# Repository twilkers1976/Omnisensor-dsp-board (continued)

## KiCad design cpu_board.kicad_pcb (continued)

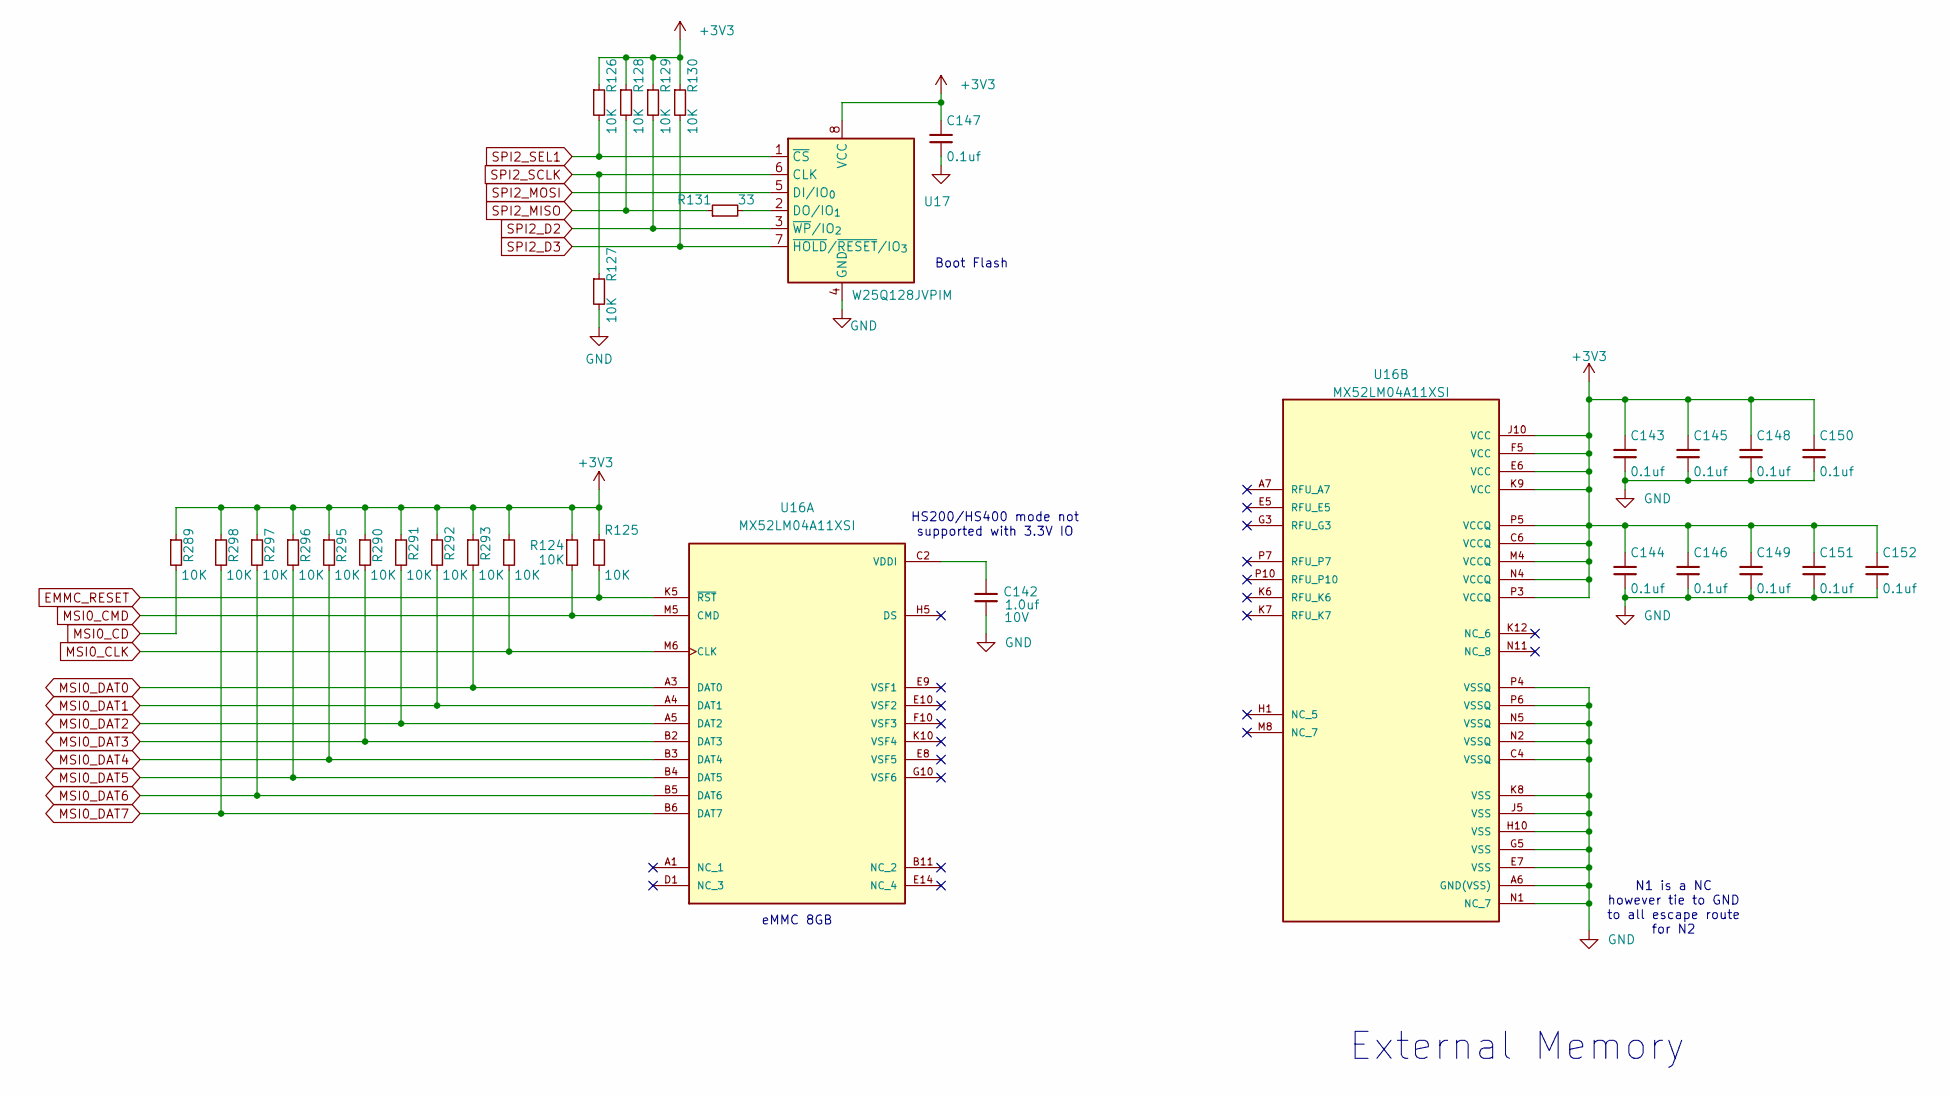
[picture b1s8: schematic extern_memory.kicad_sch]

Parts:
C142: 1.0uf; C_0402_1005Metric; Voltage 10V; Rating 16V; Part Number EMK105BJ105KV-F
C143, C144, C145, C146, C147, C148, C149, C150, C151, C152: 0.1uf; C_0402_1005Metric; Rating 50V; Part Number 04025C104KAT2A
R124, R125, R126, R127, R128, R129, R130, R289, R290, R291, R292, R293, R294, R295, R296, R297, R298: 10K; R_0402_1005Metric; Part Number RMCF0402FT10K0
R131: 33; R_0402_1005Metric; Part Number RMCF0402FT33R0
U16: MX52LM04A11XSI; BGA153N50P14X14_1300X1150X100N; PARTREV N/A
U17: W25Q128JVPIM; WSON-8-1EP_6x5mm_P1.27mm_EP3.4x4mm; Part Number W25Q128JVPIM

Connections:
+3V3: C143.1, C144.1, C145.1, C146.1, C147.1, C148.1, C149.1, C150.1, C151.1, C152.1, R124.1, R125.1, R126.1, R128.1, R129.1, R130.1, R289.1, R290.1, R291.1, R292.1, R293.1, R294.1, R295.1, R296.1, R297.1, R298.1, U16.C6 (VCCQ), U16.E6 (VCC), U16.F5 (VCC), U16.J10 (VCC), U16.K9 (VCC), U16.M4 (VCCQ), U16.N4 (VCCQ), U16.P3 (VCCQ), U16.P5 (VCCQ), U17.8 (VCC); also elsewhere on the board
EMMC_RESET: R125.2, U16.K5 (~RST); also elsewhere on the board
GND: C142.2, C143.2, C144.2, C145.2, C146.2, C147.2, C148.2, C149.2, C150.2, C151.2, C152.2, R127.2, U16.A6 (GND(VSS)), U16.C4 (VSSQ), U16.E7 (VSS), U16.G5 (VSS), U16.H10 (VSS), U16.J5 (VSS), U16.K8 (VSS), U16.N1 (NC_7), U16.N2 (VSSQ), U16.N5 (VSSQ), U16.P4 (VSSQ), U16.P6 (VSSQ), U17.4 (GND); also elsewhere on the board
MSI0_CD: R289.2; also elsewhere on the board
MSI0_CLK: R294.2, U16.M6 (CLK); also elsewhere on the board
MSI0_CMD: R124.2, U16.M5 (CMD); also elsewhere on the board
MSI0_DAT0: R293.2, U16.A3 (DAT0); also elsewhere on the board
MSI0_DAT1: R292.2, U16.A4 (DAT1); also elsewhere on the board
MSI0_DAT2: R291.2, U16.A5 (DAT2); also elsewhere on the board
MSI0_DAT3: R290.2, U16.B2 (DAT3); also elsewhere on the board
MSI0_DAT4: R295.2, U16.B3 (DAT4); also elsewhere on the board
MSI0_DAT5: R296.2, U16.B4 (DAT5); also elsewhere on the board
MSI0_DAT6: R297.2, U16.B5 (DAT6); also elsewhere on the board
MSI0_DAT7: R298.2, U16.B6 (DAT7); also elsewhere on the board
unnamed: C142.1, U16.C2 (VDDI)
unnamed: R131.2, U17.2 (DO/IO_{1})
SPI2_D2: R129.2, U17.3 (~WP/IO_{2}); also elsewhere on the board
SPI2_D3: R130.2, U17.7 (~HOLD/~RESET/IO_{3}); also elsewhere on the board
SPI2_MISO: R128.2, R131.1; also elsewhere on the board
SPI2_MOSI: U17.5 (DI/IO_{0}); also elsewhere on the board
SPI2_SCLK: R127.1, U17.6 (CLK); also elsewhere on the board
SPI2_SEL1: R126.2, U17.1 (~CS); also elsewhere on the board

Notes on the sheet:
External Memory
eMMC 8GB
HS200/HS400 mode not supported with 3.3V IO
Boot Flash
N1 is a NC however tie to GND to all escape route for N2

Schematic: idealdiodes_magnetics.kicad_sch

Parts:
C53, C140: 1000pf; C_1808_4520Metric; Voltage 3KV; Rating 3KV; Part Number CHV1808N3K0102MXT
C54: 0.047uf; C_0603_1608Metric; Voltage 16V; Rating 16V; Part Number CL10B473KO8NNNC
D1: DDZ9709S-7; Rating 24V; PARTREV 13 - 2
D2: PTVS58VS1UR,115; TVS_PTVS58VS1UR; PARTREV Rev. 3
J1: JXK0-0190NL; JK0-0177NL_PUL; Part Number JXK0-0190NL
Q1, Q2, Q3, Q4, Q5, Q6, Q7, Q8: PSMN075-100MSE; TRANS_PSMN075-100MSE; PARTREV 24 July 2024
R1, R2, R3, R4: 75; R_0603_1608Metric; Part Number RN73H1JTTD75R0F100
R5: 0; R_0402_1005Metric; Part Number RMCF0402ZT0R00
U1: LT4321IUF_PBF; PARTREV 0

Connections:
+3V3: J1.13 (CA_1), J1.16 (CA_1); also elsewhere on the board
/PoE/IdealDiodes_Magnetics/BG12: Q2.4, U1.14 (BG12)
/PoE/IdealDiodes_Magnetics/BG36: Q4.4, U1.13 (BG36)
/PoE/IdealDiodes_Magnetics/BG45: Q6.4, U1.8 (BG45)
/PoE/IdealDiodes_Magnetics/BG78: Q8.4, U1.7 (BG78)
/PoE/IdealDiodes_Magnetics/DATA1_1: J1.17 (VDC1+), Q1.1, Q1.2, Q1.3, Q2.MB, U1.15 (IN12)
/PoE/IdealDiodes_Magnetics/DATA1_2: J1.18 (VDC1=), Q3.1, Q3.2, Q3.3, Q4.MB, U1.2 (IN36)
/PoE/IdealDiodes_Magnetics/DATA2_1: J1.19 (VDC2+), Q5.1, Q5.2, Q5.3, Q6.MB, U1.3 (IN45)
/PoE/IdealDiodes_Magnetics/DATA2_2: J1.20 (VDC2-), Q7.1, Q7.2, Q7.3, Q8.MB, U1.6 (IN78)
/PoE/IdealDiodes_Magnetics/TG12: Q1.4, U1.16 (TG12)
/PoE/IdealDiodes_Magnetics/TG36: Q3.4, U1.1 (TG36)
/PoE/IdealDiodes_Magnetics/TG45: Q5.4, U1.4 (TG45)
/PoE/IdealDiodes_Magnetics/TG78: Q7.4, U1.5 (TG78)
GND: C53.2; also elsewhere on the board
LED1_CATHODE: J1.15 (CA_2); also elsewhere on the board
LED2_CATHODE: J1.14 (CA_2); also elsewhere on the board
MD1+: J1.11 (MD1+); also elsewhere on the board
MD1-: J1.10 (MD1-); also elsewhere on the board
MD2+: J1.4 (MD2+); also elsewhere on the board
MD2-: J1.5 (MD2-); also elsewhere on the board
MD3+: J1.3 (MD3+); also elsewhere on the board
MD3-: J1.2 (MD3-); also elsewhere on the board
MD4+: J1.8 (MD4+); also elsewhere on the board
MD4-: J1.9 (MD4-); also elsewhere on the board
unnamed: C53.1, R1.2, R2.2, R3.2, R4.2
unnamed: C140.1, J1.23, J1.24
unnamed: J1.12 (MDCT1), R4.1
unnamed: J1.6 (MDCT2), R3.1
unnamed: J1.1 (MDCT3), R2.1
unnamed: J1.7 (MDCT4), R1.1
unnamed: D1.A, U1.11 (EN)
unnamed: R5.1, U1.10 (~EN)
PGND: C140.2; also elsewhere on the board
VPORTN: C54.2, D2.A, Q2.1, Q2.2, Q2.3, Q4.1, Q4.2, Q4.3, Q6.1, Q6.2, Q6.3, Q8.1, Q8.2, Q8.3, U1.9 (OUTN), U1.17 (OUTN); also elsewhere on the board
VPORTP: C54.1, D1.K, D2.C, Q1.MB, Q3.MB, Q5.MB, Q7.MB, R5.2, U1.12 (OUTP); also elsewhere on the board

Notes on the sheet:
Ideal Diodes and Magnetics
do we need ESD on these, SP05045HTG
IN FROM PoE+ PSE

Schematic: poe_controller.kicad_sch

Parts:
C93: 100pf; C_0603_1608Metric; Rating 250V; Part Number CHV0603N250101FCT
C94: 0.047uf; C_0805_2012Metric; Rating 16V; Part Number C0805C473F4GACTU
C95: 0.01uf; C_0603_1608Metric; Rating 16V; Part Number KGM15AR71C103KT
C96: 10uf; PNSC-FT-V-83x83-2_V; Rating 100V; Part Number PCV2A100MCL1GS
C97: 2.2uf; C_1210_3225Metric; Rating 100V; Part Number GRM32ER72A225KA35L
C98, C107: 10uf; C_1206_3216Metric; Rating 16V; Part Number C1206C106M4RACAUTO
C99: 0.1uf; C_0603_1608Metric; Rating 50V; Part Number KGM15BR71H104KT
C100: DNP-OPT; C_0402_1005Metric; not fitted
C101: 3.3nf; C_0603_1608Metric; Rating 16V; Part Number C0603C332J4GACTU
C102: 47pf; C_1206_3216Metric; Rating 1KV; Part Number CHV1206N1K0470FCT
C103: 220pf; C_0603_1608Metric; Rating 250V; Part Number CHV0603N250221GCT
C104: 1uf; C_0603_1608Metric; Rating 50V; Part Number 06035C105KAT2A
C105: DNP-OPT; C_1812_4532Metric; Rating 2KV; not fitted
C106: 4.7nf; C_1812_4532Metric; Rating 25V; Part Number 885012210005
C108: 470pf; C_1206_3216Metric; Rating 600V; Part Number GRM31A7U2J471JW31D
C109: 2.2nf; C_0603_1608Metric; Rating 25V; Part Number GRM188R72A222KA01D
C110, C112: DNP-OPT; C_1206_3216Metric; Rating 16V; Part Number C1206C106M4RACAUTO; not fitted
C111: 22uf; CAP_16SVP22M; Rating 16V; Part Number 16SVP22M
C294: 1uf; C_0805_2012Metric; Rating 16V; Part Number CL21B105KOFVPNE
D4: B2100-13-F; DIOM5336X250N; Part Number B2100-13-F
D5, D7: PTVS58VS1UR,115; TVS_PTVS58VS1UR; Part Number PTVS58VS1UR,115
D6: BAV19WS; D_SOD-323F; Part Number BAV19WS
D8: BAT46WJ_115; SOD323_V; Part Number BAT46WJ,115
D9: DNP-OPT; SOD323_V; Part Number BAT46WJ_115; not fitted
D24: Blue; LED_B1931NG_HVK; Part Number B19Y1NB--20C000113U1930
E1: AUX+; TestPoint_THTPad_D1.0mm_Drill0.5mm; PART REFERENCE E10
E2: AUX-; TestPoint_THTPad_D1.0mm_Drill0.5mm; PART REFERENCE E10
E4: GND_SEC; TestPoint_THTPad_D1.0mm_Drill0.5mm; PART REFERENCE E10
E5: GND; TestPoint_THTPad_D1.0mm_Drill0.5mm; PART REFERENCE E10
L1: 744272332; WE-SL5_BIFILAR; Part Number 744272332
L2: 10uh; IND_DO1608C_COC; Rating 1.5A; Part Number DO1608C-103MLC
L3: 100uh; IND_DO1608C_COC; Rating 500mA; Part Number DO1608C-104MLC
L4: 330nh; DO1813H; Rating 7A; Part Number DO1813H-331MLD
Q9: PSMN075-100MSE; TRANS_PSMN075-100MSE; PARTREV 24 July 2024
Q10: FJV992FMTF; SOT91P240X120-3N; Part Number FJV992FMTF
Q11: XP10TN135N; SOT95P251X112-3N; 5TH VOLTAGE 100; PART REFERENCE Q3
Q12: BSZ520N15NS3G; SON65P330X330X110-9N; Part Number BSZ520N15NS3GATMA1
Q13: MMBT3906; SOT-23; Part Number MMBT3906
Q14: FDMC86160; TRANS_FDMC86102; 5TH VOLTAGE 100V; PART REFERENCE Q2
Q15: MMBT3904; SOT-23; Part Number MMBT3904
R70: 174K; R_0603_1608Metric; Part Number RN73H1JTTD1743F100
R71: 52.3K; R_0603_1608Metric; Part Number CPF0603F52K3C1
R72: 8.2; R_0805_2012Metric; Rating 1/4 Watt; Part Number CRCW08058R20FKEA
R73: 3.3K; R_0603_1608Metric; Rating 1/10 Watt; Part Number MCT06030C3301FP500
R74: 2K; R_0603_1608Metric; Rating 1/10 W; Part Number RN73H1JTTD2001F100
R75: 6.49K; R_0603_1608Metric; Rating 1/10 W; Part Number RN73H1JTTD6491F100
R76: DNP-OPT; R_0603_1608Metric; Rating 1/10 W; Part Number RN73H1JTTD1001F100
R77: 35.7; R_0805_2012Metric; Rating 1/4 W; Part Number CRCW080535R7FKEA
R78: 5.23K; R_0603_1608Metric; Rating 1/10 W; Part Number RN73H1JTTD5231F100
R79: 20; R_0805_2012Metric; Rating 1/4 Watt; Part Number CRCW080520R0FKEA
R80: 107K; R_0603_1608Metric; Rating 1/4 W; Part Number RN73H1JTTD1073F100
R81, R85: 0; R_0402_1005Metric; Part Number RMCF0402ZT0R00
R82: DNP-OPT; R_0603_1608Metric; Rating 1/4 W; not fitted
R83: 10K; R_0402_1005Metric; Part Number RMCF0402FT10K0
R84: 26.1K; R_0603_1608Metric; Part Number RT0603BRD0726K1L
R87: 150; R_1206_3216Metric; Rating 1/4 W; Part Number RK73H2BTTD1500F
R88: 40m; R_0603_1608Metric; Rating 1/10 W; Part Number PE0603FRF070R04L
R89: 100; R_0603_1608Metric; Rating 1/10 W; Part Number RN73H1JTTD1000F100
R90, R91: 27; R_1206_3216Metric; Rating 1/4 W; Part Number CRCW120627R0FKEAC
R92: 47K; R_0603_1608Metric; Rating 1/10 W; Part Number RN73H1JTTD4702F100
R93: 4.7K; R_0603_1608Metric; Rating 1/10 W; Part Number RN73H1JTTD4701F100
R94: 15; R_0603_1608Metric; Rating 1/10 W; Part Number RN73H1JTTD15R0F100
R95: 10K; R_0603_1608Metric; Rating 1/10W; Part Number RN73H1JTTD1002F100
R96: DNP-OPT; R_0805_2012Metric; Rating 1/4 W; not fitted
R97: 3.3K; R_0402_1005Metric; Rating 1/10 W; Part Number RMCF0402FT3K30
R100: DNP-OPT; R_1206_3216Metric; Rating 1/4 W; not fitted
R134, R142: 0; R_1210_3225Metric; Part Number RMCF1210ZT0R00
R303: 0; R_0805_2012Metric; Part Number RMCF0805ZT0R00
T1: 750310742; WE-POE__EP13_PADL1.55W1.27; Part Number 750310742
T2: PE-68386NL; PE-68386NL_PUL; Part Number PE-68386NL
U7: LT4276BIUFDTRPBF; QFN-28_UFD; Part Number LT4276BIUFD#TRPBF
U9: MOC207M; SOIC8_751DZ_ONS_OSI; Part Number MOC207M

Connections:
+3V3: R92.2; also elsewhere on the board
/PoE/PoE_Controller/PVCC: C98.1, L3.1, U7.6 (VCC), U7.7 (VCC), U7.8 (VCC), U7.9 (VCC), U7.21 (VCC)
GND: D24.1, E5.1 (A_1), R134.2, R142.2; also elsewhere on the board
GND_POWER: C93.2, C94.2, C95.2, C96.2, C97.2, C98.2, C99.2, C100.2, C103.2, C106.1, D5.A, D6.2 (A), D7.A, E2.1 (A_1), L1.3, R71.1, R74.1, R76.1, R77.1, R78.1, R80.1, R82.1, R84.1, R88.1, T1.2, T2.2, U7.1 (GND), U7.16 (ISEN-), U7.19 (GND), U7.29 (GND_EP), U9.2
GND_SEC: C106.2, C107.2, C110.2, C111.2, C112.2, C294.2, D8.2, E4.1 (A_1), Q13.3 (C), Q14.1 (S1), Q14.2 (S2), Q14.3 (S3), R90.1, R91.1, R93.2, R95.2, R134.1, T2.3, U9.5; also elsewhere on the board
unnamed: C95.1, R73.1
unnamed: C101.2, R84.2
unnamed: C102.1, R87.1, R100.1
unnamed: C104.1, R89.1
unnamed: C104.2, T2.1
unnamed: C105.2, C107.1, C110.1, L4.1, T1.9, T1.10
unnamed: C108.2, R90.2, R91.2
unnamed: C109.1, T2.4
unnamed: C109.2, D8.1, R94.1, R95.1
unnamed: D4.2 (A), R70.2
unnamed: C96.1, D4.1 (K), L2.1, Q9.1, Q9.2, Q9.3, U7.25 (HSSRC)
unnamed: D6.1 (K), L3.2, Q10.3 (E)
unnamed: D9.1, R96.1
unnamed: D24.2, R97.1
unnamed: E1.1 (A_1), L1.2, Q9.MB, R72.2
unnamed: Q10.2 (B), U7.23 (SWVCC)
unnamed: Q10.1 (C), R79.1
unnamed: C102.2, Q11.3 (DRAIN), Q12.5, Q12.6, Q12.7, Q12.8, T1.3
unnamed: Q11.1 (GATE), Q12.4, R81.2
unnamed: Q11.2 (SOURCE), Q12.1, Q12.2, Q12.3, R85.1, R88.2
unnamed: Q13.1 (B), Q15.1 (B), R94.2
unnamed: Q13.2 (E), Q14.4 (G), Q15.2 (E)
unnamed: C108.1, D9.2, Q14.5 (D1), Q14.6 (D2), Q14.7 (D3), Q14.8 (D4), T1.6, T1.7, T1.8
unnamed: C294.1, Q15.3 (C), R96.2, R303.1
unnamed: R75.2, T1.1
unnamed: R83.2, U9.1
unnamed: R93.1, U9.7
unnamed: C93.1, R70.1, R71.2, U7.2 (AUX)
unnamed: R74.2, R75.1, U7.14 (FB31)
unnamed: R78.2, U7.12 (FFSDLY)
unnamed: Q9.4, R73.2, U7.26 (HSGATE)
unnamed: C100.1, R85.2, U7.17 (ISEN+)
unnamed: C101.1, C103.1, U7.13 (ITHB)
unnamed: R81.1, U7.20 (PG)
unnamed: R77.2, U7.4 (RCLASS)
unnamed: R76.2, U7.3 (RCLASS++)
unnamed: R82.2, U7.15 (RLDCMP)
unnamed: R80.2, U7.10 (ROSC)
unnamed: C99.1, U7.11 (SFST)
unnamed: R89.2, U7.18 (SG)
unnamed: R83.1, U7.5 (T2P)
unnamed: C97.1, C105.1, D7.C, L2.2, R79.2, R87.2, R100.2, T1.5, U7.24 (VIN)
unnamed: C94.1, D5.C, R72.1, U7.28 (VPORT)
PGND: R142.1; also elsewhere on the board
POE_STATE: R92.1, U9.6; also elsewhere on the board
VIN: C111.1, C112.1, L4.2, R97.2, R303.2; also elsewhere on the board
VPORTN: L1.4; also elsewhere on the board
VPORTP: L1.1; also elsewhere on the board

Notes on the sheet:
12V/1.9A
PoE Controller
37V-57V

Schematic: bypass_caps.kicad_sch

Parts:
C7, C8, C9, C10, C11, C12: 10uf; C_0805_2012Metric; Rating 16V; Part Number EMK212BJ106KG-T
C13, C14, C15, C16, C17, C18, C19, C20, C21, C22, C23, C24, C25, C26, C27, C28, C29, C30, C31, C32, C33, C34, C37, C40: 0.1uf; C_0402_1005Metric; Rating 50V; Part Number 04025C104KAT2A
C35, C36, C38, C39, C41, C42, C43, C44, C45, C46, C47, C48, C49, C50, C51, C52, C55, C56, C57, C58, C59, C60: 0.01uf; C_0402_1005Metric; Rating 50V; Part Number 04025C103KAT2A

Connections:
+1V1: C7.1, C12.1, C15.1, C16.1, C21.1, C22.1, C27.1, C28.1, C33.1, C34.1, C37.1, C40.1, C43.1, C46.1, C49.1, C52.1, C56.1, C57.1, C58.1, C59.1, C60.1; also elsewhere on the board
+1V5: C8.1, C10.1, C13.1, C17.1, C19.1, C23.1, C25.1, C29.1, C31.1, C35.1, C38.1, C41.1, C44.1, C47.1, C50.1, C55.1; also elsewhere on the board
+3V3: C9.1, C11.1, C14.1, C18.1, C20.1, C24.1, C26.1, C30.1, C32.1, C36.1, C39.1, C42.1, C45.1, C48.1, C51.1; also elsewhere on the board
GND: C7.2, C8.2, C9.2, C10.2, C11.2, C12.2, C13.2, C14.2, C15.2, C16.2, C17.2, C18.2, C19.2, C20.2, C21.2, C22.2, C23.2, C24.2, C25.2, C26.2, C27.2, C28.2, C29.2, C30.2, C31.2, C32.2, C33.2, C34.2, C35.2, C36.2, C37.2, C38.2, C39.2, C40.2, C41.2, C42.2, C43.2, C44.2, C45.2, C46.2, C47.2, C48.2, C49.2, C50.2, C51.2, C52.2, C55.2, C56.2, C57.2, C58.2, C59.2, C60.2; also elsewhere on the board

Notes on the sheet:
DSP Bypass Caps

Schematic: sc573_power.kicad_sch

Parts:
C1, C2: 0.1uf; C_0402_1005Metric; Rating 50V; Part Number 04025C104KAT2A
U2: ADSP-SC573KBCZ-3; BC-400-2_ADI; Part Number ADSP-SC573KBCZ-3

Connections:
+1V1: U2.F5 (VDD_INT), U2.F7 (VDD_INT), U2.F8 (VDD_INT), U2.F9 (VDD_INT), U2.F10 (VDD_INT), U2.F11 (VDD_INT), U2.F12 (VDD_INT), U2.F13 (VDD_INT), U2.F14 (VDD_INT), U2.F16 (VDD_INT), U2.G5 (VDD_INT), U2.G16 (VDD_INT), U2.H5 (VDD_INT), U2.H16 (VDD_INT), U2.J5 (VDD_INT), U2.J16 (VDD_INT), U2.K5 (VDD_INT), U2.K16 (VDD_INT), U2.L5 (VDD_INT), U2.L16 (VDD_INT), U2.M5 (VDD_INT), U2.M16 (VDD_INT), U2.N5 (VDD_INT), U2.N16 (VDD_INT), U2.P5 (VDD_INT), U2.P6 (VDD_INT), U2.P8 (VDD_INT), U2.P9 (VDD_INT), U2.P10 (VDD_INT), U2.P11 (VDD_INT), U2.P12 (VDD_INT), U2.P13 (VDD_INT), U2.P15 (VDD_INT), U2.P16 (VDD_INT), U2.R4 (VDD_INT), U2.R5 (VDD_INT), U2.R7 (VDD_INT), U2.R8 (VDD_INT), U2.R9 (VDD_INT), U2.R10 (VDD_INT), U2.R11 (VDD_INT), U2.R12 (VDD_INT), U2.R13 (VDD_INT), U2.R14 (VDD_INT), U2.R16 (VDD_INT), U2.R17 (VDD_INT); also elsewhere on the board
+1V5: U2.N4 (VDD_DMC), U2.T6 (VDD_DMC), U2.T7 (VDD_DMC), U2.T8 (VDD_DMC), U2.T9 (VDD_DMC), U2.T10 (VDD_DMC), U2.T11 (VDD_DMC), U2.T12 (VDD_DMC), U2.T13 (VDD_DMC), U2.T14 (VDD_DMC), U2.T15 (VDD_DMC), U2.T17 (VDD_DMC), U2.U7 (VDD_DMC), U2.U8 (VDD_DMC), U2.U9 (VDD_DMC), U2.U10 (VDD_DMC), U2.U11 (VDD_DMC), U2.U12 (VDD_DMC), U2.U13 (VDD_DMC), U2.U14 (VDD_DMC); also elsewhere on the board
+3V3: C1.1, C2.1, U2.E7 (VDD_EXT), U2.E8 (VDD_EXT), U2.E9 (VDD_EXT), U2.E10 (VDD_EXT), U2.E11 (VDD_EXT), U2.E12 (VDD_EXT), U2.E13 (VDD_USB), U2.E17 (VDD_EXT), U2.G4 (VDD_EXT), U2.H4 (VDD_EXT), U2.H17 (VDD_EXT), U2.J4 (VDD_EXT), U2.J17 (VDD_EXT), U2.K4 (VDD_EXT), U2.K17 (VDD_EXT), U2.L4 (VDD_EXT), U2.L17 (VDD_EXT), U2.M4 (VDD_EXT), U2.M17 (VDD_EXT), U2.N17 (VDD_EXT), U2.R20 (VDD_HADC), U2.T4 (VDD_EXT), U2.U6 (VDD_EXT); also elsewhere on the board
GND: C1.2, C2.2, U2.A1 (GND), U2.A9 (GND), U2.A12 (GND), U2.A15 (GND), U2.A20 (GND), U2.B2 (GND), U2.B19 (GND), U2.C3 (GND), U2.C18 (GND), U2.D4 (GND), U2.D17 (GND), U2.E5 (GND), U2.E16 (GND), U2.F6 (GND), U2.F15 (GND), U2.G6 (GND), U2.G7 (GND), U2.G8 (GND), U2.G9 (GND), U2.G10 (GND), U2.G11 (GND), U2.G12 (GND), U2.G13 (GND), U2.G14 (GND), U2.G15 (GND), U2.H6 (GND), U2.H7 (GND), U2.H8 (GND), U2.H9 (GND), U2.H10 (GND), U2.H11 (GND), U2.H12 (GND), U2.H13 (GND), U2.H14 (GND), U2.H15 (GND), U2.J6 (GND), U2.J7 (GND), U2.J8 (GND), U2.J9 (GND), U2.J10 (GND), U2.J11 (GND), U2.J12 (GND), U2.J13 (GND), U2.J14 (GND), U2.J15 (GND), U2.K6 (GND), U2.K7 (GND), U2.K8 (GND), U2.K9 (GND), U2.K10 (GND), U2.K11 (GND), U2.K12 (GND), U2.K13 (GND), U2.K14 (GND), U2.K15 (GND), U2.L6 (GND), U2.L7 (GND), U2.L8 (GND), U2.L9 (GND), U2.L10 (GND), U2.L11 (GND), U2.L12 (GND), U2.L13 (GND), U2.L14 (GND), U2.L15 (GND), U2.L19 (GND), U2.M6 (GND), U2.M7 (GND), U2.M8 (GND), U2.M9 (GND), U2.M10 (GND), U2.M11 (GND), U2.M12 (GND), U2.M13 (GND), U2.M14 (GND), U2.M15 (GND), U2.N6 (GND), U2.N7 (GND), U2.N8 (GND), U2.N9 (GND), U2.N10 (GND), U2.N11 (GND), U2.N12 (GND), U2.N13 (GND), U2.N14 (GND), U2.N15 (GND), U2.N20 (GND), U2.P7 (GND), U2.P14 (GND), U2.R6 (GND), U2.R15 (GND), U2.T5 (GND), U2.T16 (GND), U2.U4 (GND), U2.U17 (GND), U2.V3 (GND), U2.V18 (GND), U2.W2 (GND), U2.W19 (GND), U2.Y1 (GND), U2.Y20 (GND); also elsewhere on the board

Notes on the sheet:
DSP Power

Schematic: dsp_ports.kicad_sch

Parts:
D13, D16, D21: Red; LED_B1931NG_HVK; Part Number B1911USD-20D000114U1930
D14, D17, D18, D19, D22: Green; LED_B1931NG_HVK; Part Number B1931NG--20D001114U1930
D15, D20: Yellow; LED_B1931NG_HVK; Part Number KY EELP41.22 Q2T1-36-A8J8-020-R18
D23: RGB LED; SMD4_UHD111A-FKA_CRW; Part Number UHD111A-FKA-C3K23E1L3VG5ZB3Z3
R6, R7, R8, R9, R10, R11, R12, R13, R14, R16: 3.3K; R_0402_1005Metric; Part Number RMCF0402FT3K3
R15, R17, R18, R19, R20, R21, R22, R123: 33; R_0402_1005Metric; Part Number RMCF0402FT33R0
R23, R24, R25: 1.0K; R_0402_1005Metric; Rating 1/16 W; Part Number RMCF0402FT1K00
U2: ADSP-SC573KBCZ-3; BC-400-2_ADI; Part Number ADSP-SC573KBCZ-3

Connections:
+3V3: D23.4; also elsewhere on the board
/SC573/dsp_ports/FIXED_FS: R9.2, U2.D2 (PC_08/SPI1_MISO)
/SC573/dsp_ports/FS_DYN_I: R8.2, U2.J2 (PC_07/SPI1_CLK)
/SC573/dsp_ports/FS_DYN_V: R7.2, U2.D1 (PC_06/SPI0_SEL3)
/SC573/dsp_ports/MIN_I: R10.2, U2.H2 (PC_09/SPI1_MOSI)
/SC573/dsp_ports/MIN_V: R11.2, U2.J3 (PC_10/SPI1_SEL1)
/SC573/dsp_ports/NO_TIME_SYNC: R14.2, U2.V7 (PA_08)
/SC573/dsp_ports/POWER: R16.2, U2.H3 (PC_15)
/SC573/dsp_ports/RELAY1: R6.2, U2.E1 (PC_05/SPI0_SEL2)
/SC573/dsp_ports/TIME_SYNC: R12.2, U2.C1 (PC_11/SPI1_SEL2)
/SC573/dsp_ports/TIME_SYNC_A: R13.2, U2.G1 (PC_00)
/SC573/dsp_ports/TIME_SYNC_BLU: R23.1, U2.W7 (PD_00)
/SC573/dsp_ports/TIME_SYNC_GRN: R24.1, U2.V6 (PD_01)
/SC573/dsp_ports/TIME_SYNC_RED: R25.1, U2.W6 (PD_02)
ADC_ALERT: U2.M3 (PD_09); also elsewhere on the board
ADC_CONV_SAR: U2.E2 (PE_05); also elsewhere on the board
ADC_GPIO0: U2.L2 (PD_10); also elsewhere on the board
ADC_GPIO1: U2.L1 (PD_11); also elsewhere on the board
ADC_GPIO2: U2.L3 (PD_12); also elsewhere on the board
ADC_RESET: U2.R3 (PD_08); also elsewhere on the board
ADC_SCLK: R15.1; also elsewhere on the board
ADC_SDI: U2.F2 (PC_03/SPI0_MOSI); also elsewhere on the board
ADC_SDO: U2.F1 (PC_02/SPI0_MISO); also elsewhere on the board
ADC_START: U2.K3 (ETH0_PTPAUXIN1/PD_15); also elsewhere on the board
EMMC_RESET: U2.V12 (PA_00); also elsewhere on the board
ETH0_INT: U2.W10 (PA_04); also elsewhere on the board
ETH0_MDC: U2.A4 (PA_11/ETH0_MDC); also elsewhere on the board
ETH0_MDIO: U2.A2 (PA_10/ETH0_MDIO); also elsewhere on the board
ETH0_RESET: U2.V10 (PA_02); also elsewhere on the board
ETH0_RXCLK: U2.E6 (PB_00/ETH0_RXCLK_REFCLK); also elsewhere on the board
ETH0_RXCTL: U2.C7 (PB_02/ETH0_RXCTL_RXDV); also elsewhere on the board
ETH0_RXD0: U2.B3 (PA_13/ETH0_RXD0); also elsewhere on the board
ETH0_RXD1: U2.C4 (PA_12/ETH0_RXD1); also elsewhere on the board
ETH0_RXD2: U2.C5 (PA_14/ETH0_RXD2); also elsewhere on the board
ETH0_RXD3: U2.B4 (PA_15/ETH0_RXD3); also elsewhere on the board
ETH0_TXCLK: R17.1; also elsewhere on the board
ETH0_TXCTL: R123.1; also elsewhere on the board
ETH0_TXD0: R20.1; also elsewhere on the board
ETH0_TXD1: R21.1; also elsewhere on the board
ETH0_TXD2: R19.1; also elsewhere on the board
ETH0_TXD3: R18.1; also elsewhere on the board
GND: D13.1, D14.1, D15.1, D16.1, D17.1, D18.1, D19.1, D20.1, D21.1, D22.1; also elsewhere on the board
MSI0_CD: U2.B1 (PC_12/MSI0_CD); also elsewhere on the board
MSI0_CLK: R22.2; also elsewhere on the board
MSI0_CMD: U2.B20 (MSi0_CMD/PF_07); also elsewhere on the board
MSI0_DAT0: U2.D16 (MSI0_D0/PE_12); also elsewhere on the board
MSI0_DAT1: U2.D15 (MSI0_D1/PE_13); also elsewhere on the board
MSI0_DAT2: U2.C17 (MSI0_D2/PE_14); also elsewhere on the board
MSI0_DAT3: U2.E15 (MSI0_D3/PE_15); also elsewhere on the board
MSI0_DAT4: U2.B16 (MSI0_D4/PF_00); also elsewhere on the board
MSI0_DAT5: U2.B17 (MSI0_D5/PF_01); also elsewhere on the board
MSI0_DAT6: U2.F17 (MSI0_D6/PF_02); also elsewhere on the board
MSI0_DAT7: U2.A18 (MSI0_D7/PF_03); also elsewhere on the board
unnamed: D13.2, R6.1
unnamed: D14.2, R7.1
unnamed: D15.2, R8.1
unnamed: D16.2, R9.1
unnamed: D17.2, R10.1
unnamed: D18.2, R11.1
unnamed: D19.2, R12.1
unnamed: D20.2, R13.1
unnamed: D21.2, R14.1
unnamed: D22.2, R16.1
unnamed: D23.1, R23.2
unnamed: D23.2, R24.2
unnamed: D23.3, R25.2
unnamed: R22.1, U2.E18 (MSI0_CLK/PF_04)
unnamed: R17.2, U2.B6 (PB_04/ETH0_TXCLK)
unnamed: R18.2, U2.C10 (PB_05/ETH0_TXD3)
unnamed: R19.2, U2.C9 (PB_06/ETH0_TXD2)
unnamed: R20.2, U2.D9 (PB_07/ETH0_TXD0)
unnamed: R21.2, U2.D8 (PB_08/ETH0_TXD1)
unnamed: R123.2, U2.D10 (PB_09/ETH0_TXCTL_TXEN)
unnamed: R15.2, U2.G3 (PC_01/SPI0_CLK)
PB1: U2.R1 (UART0_CTS/PD_06); also elsewhere on the board
PB2: U2.R2 (PD_07); also elsewhere on the board
POE_STATE: U2.V11 (PA_01); also elsewhere on the board
PPS_INPUT: U2.G2 (PC_14/_TM0_ACI3), U2.K1 (ETH0_PTPAUXIN0/PD_14); also elsewhere on the board
PPS_OUTPUT: U2.A3 (PA_09/ETH0_PTPPPS0), U2.B5 (PB_01/ETH0_CRS/_TM0_TMR3); also elsewhere on the board
PPS_OUTPUT_EN: U2.W9 (PA_06); also elsewhere on the board
RANGE_1: U2.J1 (PE_00); also elsewhere on the board
RANGE_2: U2.H1 (PE_01); also elsewhere on the board
RANGE_3: U2.E4 (PE_02); also elsewhere on the board
RANGE_4: U2.E3 (PE_03); also elsewhere on the board
RANGE_AUTO: U2.D3 (PE_04); also elsewhere on the board
RELAY_DRV: U2.V9 (PA_03); also elsewhere on the board
SI5351_SSEN: U2.V4 (PD_03); also elsewhere on the board
SPI2_D2: U2.C14 (PB_12/SPI2_D2); also elsewhere on the board
SPI2_D3: U2.C15 (PB_13/SPI2_D3); also elsewhere on the board
SPI2_MISO: U2.B13 (PB_10/SPI2_MISO); also elsewhere on the board
SPI2_MOSI: U2.D12 (PB_11/SPI2_MOSI); also elsewhere on the board
SPI2_SCLK: U2.D14 (PB_14/SPI2_CLK); also elsewhere on the board
SPI2_SEL1: U2.G17 (PB_15/SPI2_SEL1); also elsewhere on the board
USB_UART0_CTS: U2.T1 (UART0_RTS/PD_05); also elsewhere on the board
USB_UART0_RTS: U2.V5 (PD_04); also elsewhere on the board
USB_UART0_RX: U2.F18 (UART0_RX/PF_09); also elsewhere on the board
USB_UART0_TX: U2.C19 (UART0_TX/PF_08); also elsewhere on the board
ZERO_CROSS_I: U2.C20 (UART1_RX/PF_11); also elsewhere on the board
ZERO_CROSS_V: U2.C2 (PC_13/MSI0_INT); also elsewhere on the board
~ADC_CS: U2.F3 (PC_04/SPI0_SEL1); also elsewhere on the board
~PPS_INPUT_EN: U2.V8 (PA_05); also elsewhere on the board

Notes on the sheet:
STATUS LEDs
TIME SYNC STATUS
SC573 Muxed IO

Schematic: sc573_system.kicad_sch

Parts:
C3, C4, C5, C6: 0.1uf; C_0402_1005Metric; Rating 50V; Part Number 04025C104KAT2A
D3: 1SS389,L3F; D_SOD-523; Part Number 1SS389,L3F
J2: BMODE; PinHeader_1x03_P2.00mm_Vertical; Part Number 2PH1-03-UA
J3: JTAG; CNC_3220-10-0300-00; Part Number 3220-10-0300-00
R26, R27, R28, R29, R34, R37, R38, R48, R49, R50, R51, R52, R120: 10K; R_0402_1005Metric; Part Number RMCF0402FT10K0
R30, R32, R133: DNP-33; R_0402_1005Metric; Part Number RMCF0402FT33R0; not fitted
R31, R33, R35, R39, R40, R41: 33; R_0402_1005Metric; Part Number RMCF0402FT33R0
R43, R44, R46, R47: 2K; R_0402_1005Metric; Part Number RMCF0402FT2K00
R45: 0; R_0402_1005Metric; Part Number RMCF0402ZT0R00
R53, R63: DNP-10K; R_0402_1005Metric; Part Number RMCF0402FT10K; not fitted
S1: R-667843; R-667843_MIT; PARTREV 14 Apr 22
U2: ADSP-SC573KBCZ-3; BC-400-2_ADI; Part Number ADSP-SC573KBCZ-3
U3: SI5351B-B-GM; QFN50P400X400X90-21N; PARTREV 1.0
U4: ADM6315; RA_4_ADI; PARTREV 5
Y1: 25 Mhz; CRYSTAL_4SMD_3.2MM_2.5MM; Part Number ABM8-25.000MHZ-10-B1U-T
Y2: 25 Mhz; OSC_4SMD_2.5MM_2.0MM; Part Number ECS-2520S33-250-FN-TR

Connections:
+3V3: C3.1, C4.1, C5.1, C6.1, J2.2, J3.1, R26.1, R27.1, R29.1, R43.1, R44.1, R46.1, R47.1, R48.1, R49.1, R50.1, R51.1, R53.1, U3.10 (VDDOB), U3.11 (VDDOA), U3.14 (VDDOD), U3.18 (VDDOC), U3.20 (VDD), U4.4 (VCC), Y2.4 (VCC); also elsewhere on the board
/SC573/sc573_system/JTG_TCK: J3.4, R51.2, U2.E14 (JTG_TCK)
/SC573/sc573_system/JTG_TDI: J3.8, R48.2, U2.C16 (JTG_TDI)
/SC573/sc573_system/JTG_TDO: J3.6, R49.2, U2.B14 (JTG_TDO)
/SC573/sc573_system/JTG_TMS: J3.2, R50.2, U2.B15 (JTG_TMS)
/SC573/sc573_system/JTG_TRST: J3.9, R52.1, U2.B10 (JTG_TRST*)
/SC573/sc573_system/SYSCLK0: R30.2, R35.2, U2.A11 (SYS_CLKIN0)
/SC573/sc573_system/SYSCLK1: R31.2, U2.A14 (SYS_CLKIN1)
/SC573/sc573_system/TARGET_RESET: J3.10, R26.2, S1.A1, S1.A2, U4.3 (~MR)
/SC573/sc573_system/USB_CLK: R33.2, U2.C13 (USB0_CLKIN)
/SC573/sc573_system/~HWRST: R29.2, U2.C11 (SYS_HWRST*), U4.2 (~RST)
ADC_D0: U2.D19 (DAI0_PIN01); also elsewhere on the board
ADC_D1: U2.F19 (DAI0_PIN02); also elsewhere on the board
ADC_D2: U2.H18 (DAI0_PIN05); also elsewhere on the board
ADC_D3: U2.F20 (DAI0_PIN06); also elsewhere on the board
ADC_DCLK: U2.E20 (DAI0_PIN03); also elsewhere on the board
ADC_MCLK: R32.2, U2.H20 (DAI0_PIN11); also elsewhere on the board
DAC_CLK: R39.1; also elsewhere on the board
DAC_DATA: R41.1; also elsewhere on the board
DAC_FS: R40.1; also elsewhere on the board
ETH0_CLKIN: R133.2; also elsewhere on the board
GND: C3.2, C4.2, C5.2, C6.2, J3.3, J3.5, R28.2, R34.2, R37.2, R38.2, R45.1, R52.2, R63.2, R120.2, S1.B1, S1.B2, U3.3 (VC), U3.7 (OEB), U3.21 (GND), U4.1 (VSS), Y1.2 (GND), Y1.4 (GND), Y2.2 (GND); also elsewhere on the board
unnamed: D3.2 (A), J2.1, R34.1, U2.W18 (SYS_BMODE1)
unnamed: D3.1 (K), J2.3, R28.1, U2.Y18 (SYS_BMODE0)
unnamed: R37.1, U2.Y19 (SYS_BMODE2)
unnamed: R38.1, U2.V14 (SYS_FAULT)
unnamed: R39.2, U2.G18 (DAI0_PIN08)
unnamed: R40.2, U2.G20 (DAI0_PIN09)
unnamed: R41.2, U2.G19 (DAI0_PIN10)
unnamed: R45.2, U2.P20 (HADC0_VREFN)
unnamed: R53.2, R63.1, U2.C12 (USB0_ID)
unnamed: R30.1, U3.13 (CLK0)
unnamed: R31.1, U3.9 (CLK2)
unnamed: R32.1, U3.19 (CLK4)
unnamed: R33.1, U3.16 (CLK6)
unnamed: R133.1, U3.15 (CLK7)
unnamed: U3.1 (XA), Y1.1
unnamed: U3.2 (XB), Y1.3
unnamed: R27.2, Y2.1 (EN)
unnamed: R35.1, Y2.3 (OUT)
SI5351_SSEN: U3.6 (SSEN); also elsewhere on the board
TWI0_SCL: R44.2, U2.T3 (TWI0_SCL), U3.4 (SCL); also elsewhere on the board
TWI0_SDA: R43.2, U2.T2 (TWI0_SDA), U3.5 (SDA); also elsewhere on the board
TWI2_SCL: R47.2, U2.W1 (TWI2_SCL); also elsewhere on the board
TWI2_SDA: R46.2, U2.V1 (TWI2_SDA); also elsewhere on the board
USB0_DN: U2.A17 (USB0_DM); also elsewhere on the board
USB0_DP: U2.A16 (USB0_DP); also elsewhere on the board
USB0_VBC: R120.1, U2.D13 (USB0_VBC); also elsewhere on the board
USB_VBUS: U2.B11 (USB0_VBUS); also elsewhere on the board
~ADC_DRDY: U2.D20 (DAI0_PIN04); also elsewhere on the board

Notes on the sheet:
SC573 Un-Muxed Peripherals
DSP Reset

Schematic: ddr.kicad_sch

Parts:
C61, C63, C65, C66, C67, C68, C69, C70, C87, C88, C89, C91: 0.1uf; C_0402_1005Metric; Rating 50V; Part Number 04025C104KAT2A
C62, C71, C74: 10uf; C_0603_1608Metric; Rating 16V; Part Number GRM188R61C106MAALD
C64: 1.0uf; C_0402_1005Metric; Rating 16V; Part Number EMK105BJ105KV-F
C72: 22uf; C_0603_1608Metric; Rating 6.3V; Part Number C1608X5R0J226M080AC
C73: 4.7uf; C_0402_1005Metric; Rating 6.3V; Part Number JMK105BBJ475MV-F
C75: 220uf; C_1206_3216Metric; Rating 6.3V; Part Number GMC31X5R227M6R3NT
C76, C77, C79, C80, C81, C82, C83, C84, C85, C86, C90, C92: 0.01uf; C_0402_1005Metric; Rating 50V; Part Number 04025C103KAT2A
C78: 100pf; C_0402_1005Metric; Rating 50V; Part Number KGM05AR71H101KH
R54, R55, R56, R57, R58: 100; R_0402_1005Metric; Part Number RMCF0402FT100R
R59: 0; R_0402_1005Metric; Part Number RMCF0402ZT0R00
R60: DNP-0; R_0603_1608Metric; Part Number RMCF0603FT0R; not fitted
R61: 2K; R_0402_1005Metric; Part Number RMCF0402FT2K0
R62: 33; R_0402_1005Metric; Part Number RMCF0402FT33R0
R64: 34; R_0402_1005Metric; Part Number RMCF0402FT34R0
R65: 240; R_0402_1005Metric; Part Number RMCF0402FT240R
R66, R67, R68: 1.0K; R_0402_1005Metric; Rating 1/16 W; Part Number RMCF0402FT1K00
R69: 200; R_0402_1005Metric; Part Number RMCF0402FT200R
R86: 10K; R_0402_1005Metric; Part Number RMCF0402FT10K0
RN1, RN2, RN3, RN4, RN5, RN6: 100 ohm; RESCAXS50P200X100X45-8N; Part Number EXB-28V101JX
U2: ADSP-SC573KBCZ-3; BC-400-2_ADI; Part Number ADSP-SC573KBCZ-3
U5: MIC5166YML-TR; MLF-10_ML_MCH; Part Number MIC5166YML-TR
U6: IS43TR16128DL-125KBL; BGA80P96C6X16_800X1400X110; Part Number IS43TR16128DL-125KBL

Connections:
+1V5: C61.1, C62.1, C63.1, C65.1, C67.1, C68.1, C69.1, C70.1, C87.1, R67.2, R86.1, U5.4 (VDDQ), U6.A1 (VDDQ), U6.A8 (VDDQ), U6.B2 (VDD), U6.C1 (VDDQ), U6.C9 (VDDQ), U6.D2 (VDDQ), U6.D9 (VDD), U6.E9 (VDDQ), U6.F1 (VDDQ), U6.G7 (VDD), U6.H2 (VDDQ), U6.H9 (VDDQ), U6.K2 (VDD), U6.K8 (VDD), U6.N1 (VDD), U6.N9 (VDD), U6.R1 (VDD), U6.R9 (VDD); also elsewhere on the board
+3V3: C64.1, C71.2, R59.1, U5.2 (BIAS), U5.10 (VIN); also elsewhere on the board
/SC573/ddr/DMC0_A00: RN6.3 (R3.1), U2.U20 (DMC0_A00), U6.N3 (A0)
/SC573/ddr/DMC0_A01: RN2.1 (R1.1), U2.T19 (DMC0_A01), U6.P7 (A1)
/SC573/ddr/DMC0_A02: RN6.2 (R2.1), U2.T18 (DMC0_A02), U6.P3 (A2)
/SC573/ddr/DMC0_A03: R56.1, U2.U19 (DMC0_A03), U6.N2 (A3)
/SC573/ddr/DMC0_A04: RN1.3 (R3.1), U2.V19 (DMC0_A04), U6.P8 (A4)
/SC573/ddr/DMC0_A05: R57.1, U2.V20 (DMC0_A05), U6.P2 (A5)
/SC573/ddr/DMC0_A06: RN1.2 (R2.1), U2.U18 (DMC0_A06), U6.R8 (A6)
/SC573/ddr/DMC0_A07: RN4.1 (R1.1), U2.W20 (DMC0_A07), U6.R2 (A7)
/SC573/ddr/DMC0_A08: RN2.4 (R4.1), U2.W17 (DMC0_A08), U6.T8 (A8)
/SC573/ddr/DMC0_A09: RN6.1 (R1.1), U2.P3 (DMC0_A09), U6.R3 (A9)
/SC573/ddr/DMC0_A10: RN3.2 (R2.1), U2.P4 (DMC0_A10), U6.L7 (A10/AP)
/SC573/ddr/DMC0_A11: RN2.3 (R3.1), U2.N1 (DMC0_A11), U6.R7 (A11)
/SC573/ddr/DMC0_A12: R58.1, U2.N3 (DMC0_A12), U6.N7 (A12/~BC)
/SC573/ddr/DMC0_A13: RN4.3 (R3.1), U2.N2 (DMC0_A13), U6.T3 (A13)
/SC573/ddr/DMC0_A14: RN2.2 (R2.1), U2.M1 (DMC0_A14), U6.T7 (NC(A14))
/SC573/ddr/DMC0_A15: RN3.1 (R1.1), U2.M2 (DMC0_A15), U6.M7 (NC(A15))
/SC573/ddr/DMC0_BA0: R55.1, U2.R18 (DMC0_BA0), U6.M2 (BA0)
/SC573/ddr/DMC0_BA1: RN1.4 (R4.1), U2.V17 (DMC0_BA1), U6.N8 (BA1)
/SC573/ddr/DMC0_BA2: RN6.4 (R4.1), U2.U15 (DMC0_BA2), U6.M3 (BA2)
/SC573/ddr/DMC0_CAS*: RN5.3 (R3.1), U2.V15 (DMC0_CAS*), U6.K3 (~CAS)
/SC573/ddr/DMC0_CKE: RN3.3 (R3.1), U2.Y16 (DMC0_CKE), U6.K9 (CKE)
/SC573/ddr/DMC0_CKN: R69.2, U2.Y9 (DMC0_CK*), U6.K7 (~CK)
/SC573/ddr/DMC0_CKP: R69.1, U2.Y8 (DMC0_CK), U6.J7 (CK)
/SC573/ddr/DMC0_CS0: RN5.2 (R2.1), U2.Y17 (DMC0_CS0*), U6.L2 (~CS)
/SC573/ddr/DMC0_DQ00: U2.Y15 (DMC0_DQ00), U6.E3 (DQ0)
/SC573/ddr/DMC0_DQ01: U2.Y14 (DMC0_DQ01), U6.F7 (DQ1)
/SC573/ddr/DMC0_DQ02: U2.W14 (DMC0_DQ02), U6.F2 (DQ2)
/SC573/ddr/DMC0_DQ03: U2.W13 (DMC0_DQ03), U6.F8 (DQ3)
/SC573/ddr/DMC0_DQ04: U2.W12 (DMC0_DQ04), U6.H3 (DQ4)
/SC573/ddr/DMC0_DQ05: U2.W11 (DMC0_DQ05), U6.H8 (DQ5)
/SC573/ddr/DMC0_DQ06: U2.Y11 (DMC0_DQ06), U6.G2 (DQ6)
/SC573/ddr/DMC0_DQ07: U2.Y10 (DMC0_DQ07), U6.H7 (DQ7)
/SC573/ddr/DMC0_DQ08: U2.Y5 (DMC0_DQ08), U6.D7 (DQ8)
/SC573/ddr/DMC0_DQ09: U2.W5 (DMC0_DQ09), U6.C3 (DQ9)
/SC573/ddr/DMC0_DQ10: U2.Y4 (DMC0_DQ10), U6.C8 (DQ10)
/SC573/ddr/DMC0_DQ11: U2.W4 (DMC0_DQ11), U6.C2 (DQ11)
/SC573/ddr/DMC0_DQ12: U2.W3 (DMC0_DQ12), U6.A7 (DQ12)
/SC573/ddr/DMC0_DQ13: U2.V2 (DMC0_DQ13), U6.A2 (DQ13)
/SC573/ddr/DMC0_DQ14: U2.U2 (DMC0_DQ14), U6.B8 (DQ14)
/SC573/ddr/DMC0_DQ15: U2.U1 (DMC0_DQ15), U6.A3 (DQ15)
/SC573/ddr/DMC0_LDM: U2.Y7 (DMC0_LDM), U6.E7 (LDM)
/SC573/ddr/DMC0_LDQSN: U2.Y13 (DMC0_LDQS*), U6.G3 (~LDQS)
/SC573/ddr/DMC0_LDQSP: U2.Y12 (DMC0_LDQS), U6.F3 (LDQS)
/SC573/ddr/DMC0_ODT: R54.1, U2.W16 (DMC0_ODT), U6.K1 (ODT)
/SC573/ddr/DMC0_RAS*: RN5.4 (R4.1), U2.V16 (DMC0_RAS*), U6.J3 (~RAS)
/SC573/ddr/DMC0_RESET: R62.2, R86.2, RN4.2 (R2.1), U6.T2 (~RESET)
/SC573/ddr/DMC0_RZQ: R64.1, U2.P2 (DMC0_RZQ)
/SC573/ddr/DMC0_UDM: U2.Y6 (DMC0_UDM), U6.D3 (UDM)
/SC573/ddr/DMC0_UDQSN: U2.Y2 (DMC0_UDQS*), U6.B7 (~UDQS)
/SC573/ddr/DMC0_UDQSP: U2.Y3 (DMC0_UDQS), U6.C7 (UDQS)
/SC573/ddr/DMC0_WE: RN5.1 (R1.1), U2.U16 (DMC0_WE), U6.L3 (~WE)
/SC573/ddr/VTT: C72.1, C73.1, C74.1, C75.1, C76.1, C77.1, C79.1, C80.1, C81.1, C82.1, C83.1, C84.1, C85.1, C86.1, R54.2, R55.2, R56.2, R57.2, R58.2, RN1.5 (R4.2), RN1.6 (R3.2), RN1.7 (R2.2), RN1.8 (R1.2), RN2.5 (R4.2), RN2.6 (R3.2), RN2.7 (R2.2), RN2.8 (R1.2), RN3.6 (R3.2), RN3.7 (R2.2), RN3.8 (R1.2), RN4.6 (R3.2), RN4.7 (R2.2), RN4.8 (R1.2), RN5.5 (R4.2), RN5.6 (R3.2), RN5.7 (R2.2), RN5.8 (R1.2), RN6.5 (R4.2), RN6.6 (R3.2), RN6.7 (R2.2), RN6.8 (R1.2), U5.6 (SNS), U5.9 (VTT)
/SC573/ddr/_DMC0_VREF: C66.1, R60.1, U5.1 (VREF)
GND: C61.2, C62.2, C63.2, C64.2, C65.2, C66.2, C67.2, C68.2, C69.2, C70.2, C71.1, C72.2, C73.2, C74.2, C75.2, C76.2, C77.2, C78.2, C79.2, C80.2, C81.2, C82.2, C83.2, C84.2, C85.2, C86.2, C88.2, C89.2, C90.2, C91.2, C92.2, R64.2, R65.2, R68.1, U5.3 (AGND), U5.8 (PGND), U5.11 (EPAD), U6.A9 (VSS), U6.B1 (VSSQ), U6.B3 (VSS), U6.B9 (VSSQ), U6.D1 (VSSQ), U6.D8 (VSSQ), U6.E1 (VSS), U6.E2 (VSSQ), U6.E8 (VSSQ), U6.F9 (VSSQ), U6.G1 (VSSQ), U6.G8 (VSS), U6.G9 (VSSQ), U6.J2 (VSS), U6.J8 (VSS), U6.M1 (VSS), U6.M9 (VSS), U6.P1 (VSS), U6.P9 (VSS), U6.T1 (VSS), U6.T9 (VSS); also elsewhere on the board
unnamed: C78.1, R60.2, R61.1, R66.1
unnamed: R62.1, U2.T20 (DMC0_RESET*)
unnamed: R61.2, U2.P1 (DMC0_VREF)
unnamed: R59.2, U5.7 (EN)
unnamed: C87.2, C88.1, C89.1, C90.1, C91.1, C92.1, R66.2, R67.1, R68.2, U6.H1 (VREFDQ), U6.M8 (VREFCA)
unnamed: R65.1, U6.L8 (ZQ)

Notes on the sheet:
keep on opposite layer as Buck converter with current layou
DDR3
